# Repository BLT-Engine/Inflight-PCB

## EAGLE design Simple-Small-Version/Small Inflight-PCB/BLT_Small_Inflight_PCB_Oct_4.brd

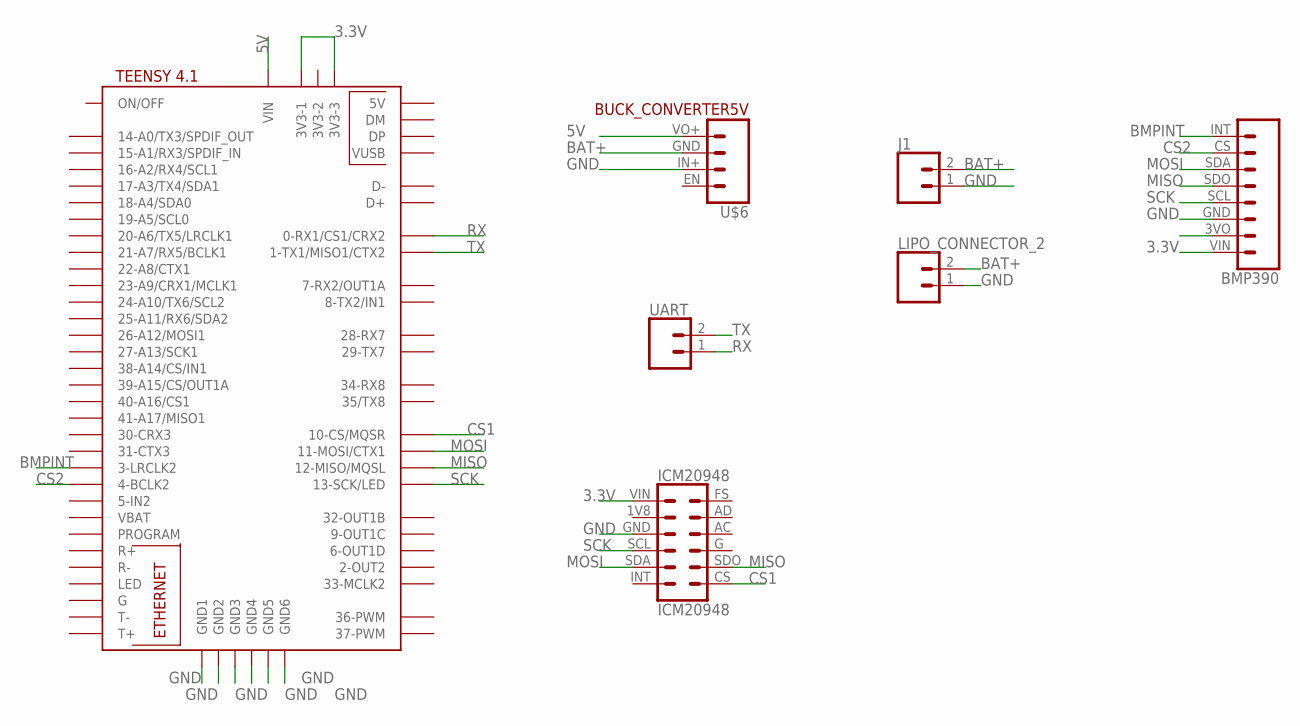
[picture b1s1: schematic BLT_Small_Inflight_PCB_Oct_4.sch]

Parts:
J1: CONN_02PTH4; 1X02_XTRA_BIG
LIPO_CONNECTOR_2: CONN_02; 1X02
U$1: TEENSY41
U$2: BMP390; MICROBUILDER_1X08_ROUND
U$3: ICM20948
U$6: BUCK_CONVERTER5V; 1X04
UART: CONN_02; 1X02

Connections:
3.3V: U$1.3V3-1, U$1.3V3-3, U$2.VIN, U$3.VIN
5V: U$1.VIN, U$6.VO+
BAT+: J1.2, LIPO_CONNECTOR_2.2, U$6.IN+
BMPINT: U$1.3-LRCLK2, U$2.INT
CS1: U$1.10-CS\MQSR (10-CS/MQSR), U$3.CS
CS2: U$1.4-BCLK2, U$2.CS
GND: J1.1, LIPO_CONNECTOR_2.1, U$1.GND1, U$1.GND2, U$1.GND3, U$1.GND4, U$1.GND5, U$1.GND6, U$2.GND, U$3.GND, U$6.GND
MISO: U$1.12-MISO/MQSL, U$2.SDO, U$3.SDO (SD0)
MOSI: U$1.11-MOSI/CTX1, U$2.SDA, U$3.SDA
RX: U$1.0-RX1/CS1/CRX2, UART.1
SCK: U$1.13-SCK/LED, U$2.SCL, U$3.SCL
TX: U$1.1-TX1/MISO1/CTX2, UART.2

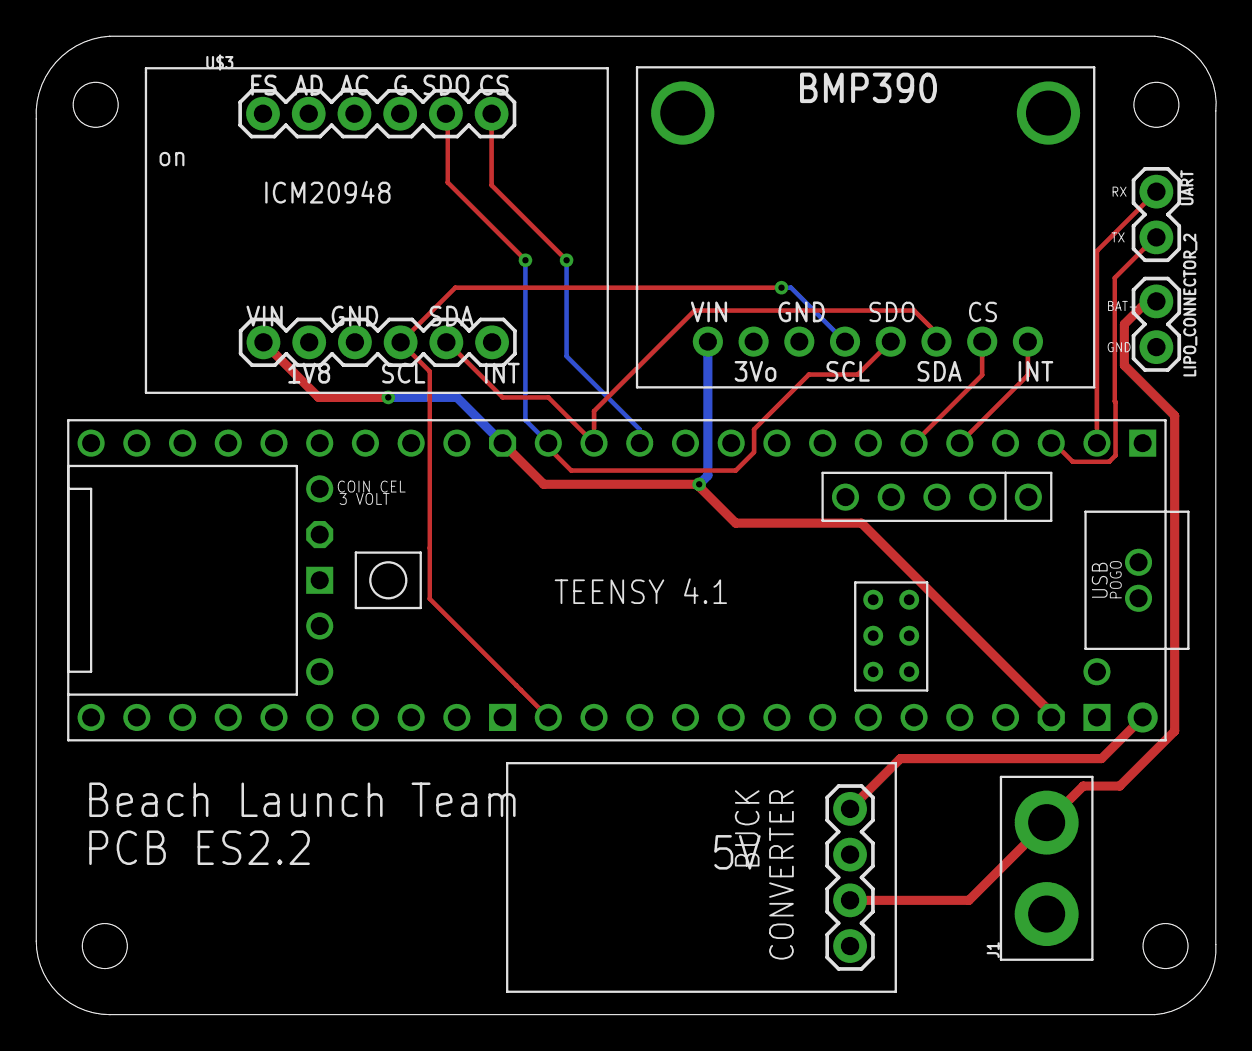
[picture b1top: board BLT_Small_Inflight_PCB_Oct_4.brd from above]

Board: 2 copper layers, 65.6 x 54.4 mm, 7 parts (0 on the bottom side), 12 nets.

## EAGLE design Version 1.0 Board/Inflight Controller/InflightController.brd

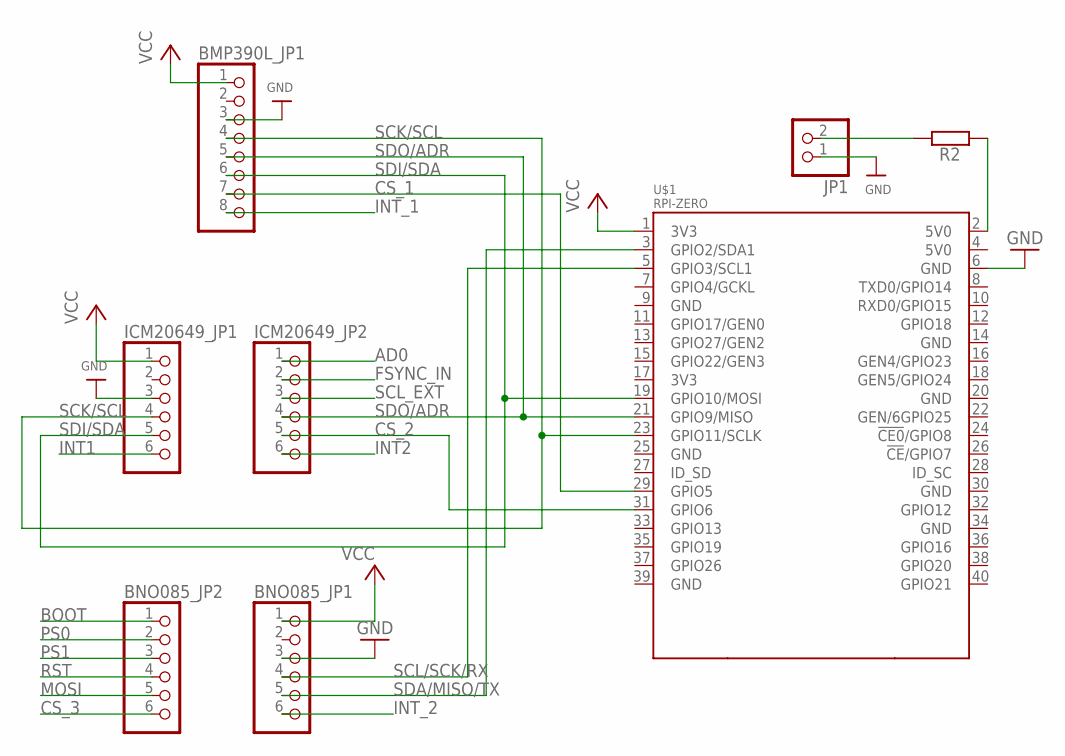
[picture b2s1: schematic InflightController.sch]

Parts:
BMP390L_JP1: HEADER-1X870MIL; 1X08_ROUND_70
BNO085_JP1, BNO085_JP2: HEADER-1X670MIL; 1X06_ROUND_70
ICM20649_JP1: HEADER-1X670MIL; 1X06_ROUND_70
ICM20649_JP2: HEADER-1X6ROUND; 1X06_ROUND
JP1: PINHD-1X2; 1X02
R2: SMK
U$1: RPI-ZERO; RASPBERRYPI_BASTELSTUBE_V13_RASPI_BOARD_B+_FULL

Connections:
5V0@1: R2.2, U$1.2 (5V0)
AD0: ICM20649_JP2.1
BOOT: BNO085_JP2.1
CS_1: BMP390L_JP1.7, U$1.29 (GPIO5)
CS_2: ICM20649_JP2.5, U$1.31 (GPIO6)
CS_3: BNO085_JP2.6
FSYNC_IN: ICM20649_JP2.2
GND: BMP390L_JP1.3, BNO085_JP1.3, ICM20649_JP1.3, JP1.1, U$1.6 (GND)
INT1: ICM20649_JP1.6
INT2: ICM20649_JP2.6
INT_1: BMP390L_JP1.8
INT_2: BNO085_JP1.6
MOSI: BNO085_JP2.5
unnamed: JP1.2, R2.1
PS0: BNO085_JP2.2
PS1: BNO085_JP2.3
RST: BNO085_JP2.4
SCK/SCL: BMP390L_JP1.4, ICM20649_JP1.4, U$1.23 (GPIO11/SCLK)
SCL/SCK/RX: BNO085_JP1.4, U$1.5 (GPIO3/SCL1)
SCL_EXT: ICM20649_JP2.3
SDA/MISO/TX: BNO085_JP1.5, U$1.3 (GPIO2/SDA1)
SDI/SDA: BMP390L_JP1.6, ICM20649_JP1.5, U$1.19 (GPIO10/MOSI)
SDO/ADR: BMP390L_JP1.5, ICM20649_JP2.4, U$1.21 (GPIO9/MISO)
VCC: BMP390L_JP1.1, BNO085_JP1.1, ICM20649_JP1.1, U$1.1 (3V3)

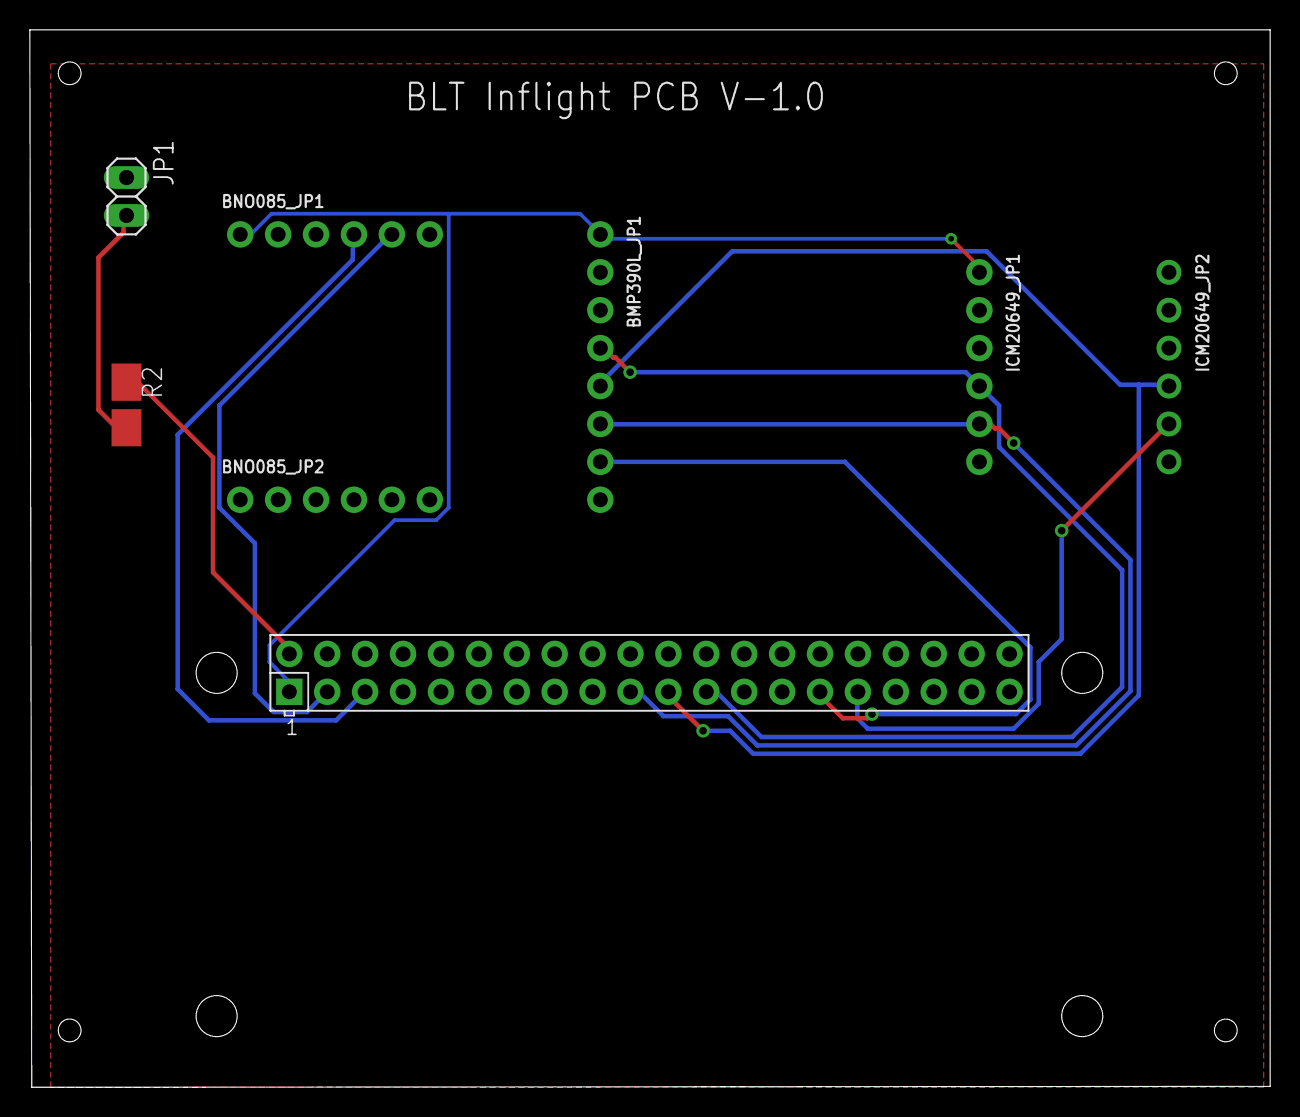
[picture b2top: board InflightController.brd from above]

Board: 2 copper layers, 83.1 x 70.9 mm, 8 parts (0 on the bottom side), 11 nets.

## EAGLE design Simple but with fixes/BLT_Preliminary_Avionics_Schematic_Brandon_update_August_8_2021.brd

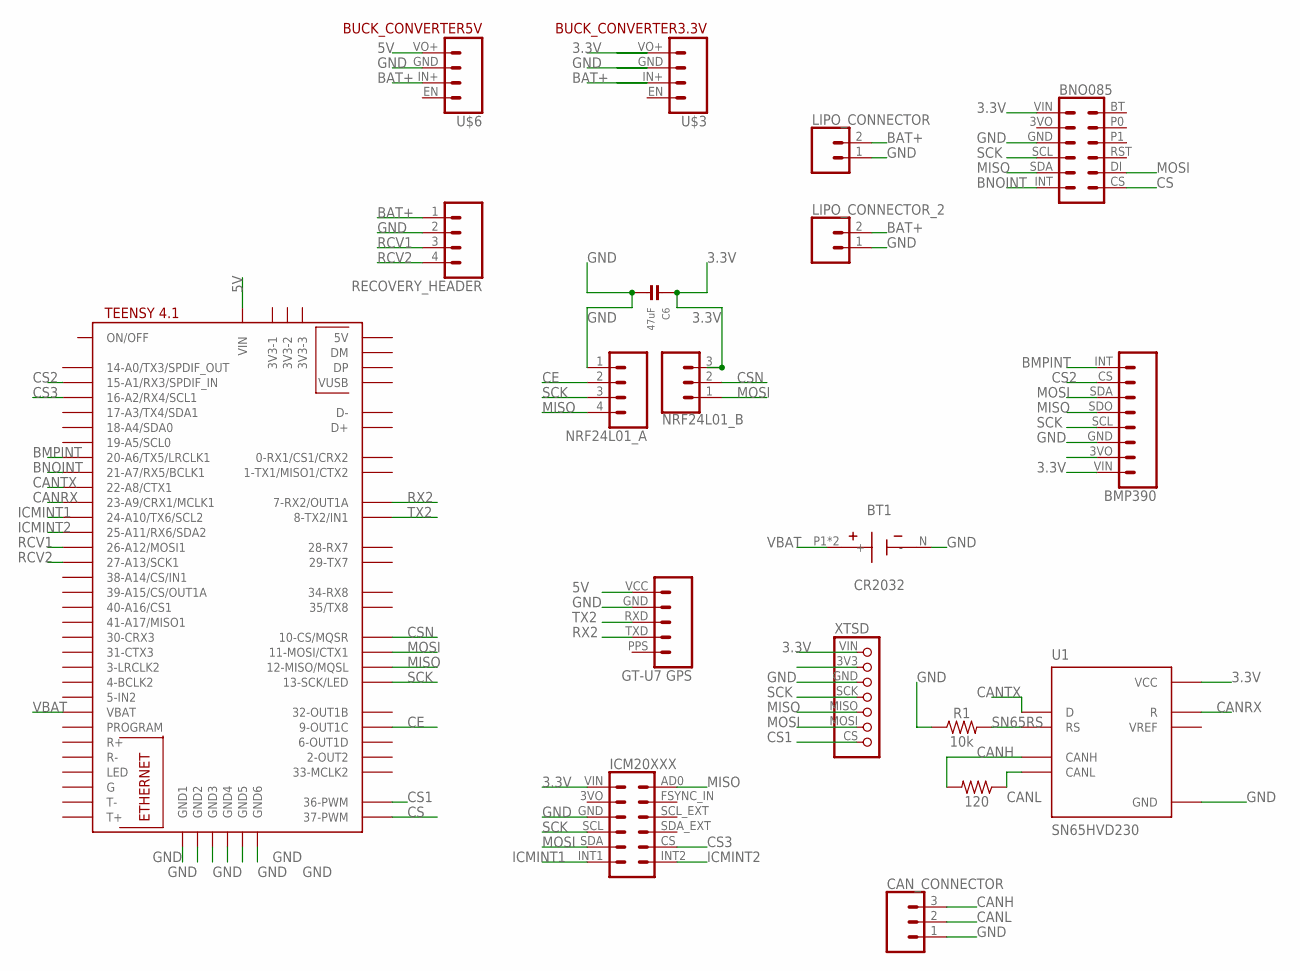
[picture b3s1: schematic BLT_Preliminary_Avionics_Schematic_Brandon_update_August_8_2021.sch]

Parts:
120: 1206
BT1: CR2032; BAT_3003
C6: 47uF; 0805
CAN_CONNECTOR: CONN_03; 1X03
LIPO_CONNECTOR: CONN_02PTH4; 1X02_XTRA_BIG
LIPO_CONNECTOR_2: CONN_02; 1X02
NRF24L01_A: CONN_04; 1X04
NRF24L01_B: CONN_03; 1X03
R1: 10k; 0603
RECOVERY_HEADER: CONN_04; 1X04
U1: SN65HVD230; SOIC127P599X175-8N
U$1: TEENSY41
U$2: BMP390; MICROBUILDER_1X08_ROUND
U$3: BUCK_CONVERTER3.3V; 1X04
U$4: GT-U7_GPS; 1X05
U$5: XTSDXTSD_PINS; 1X07
U$6: BUCK_CONVERTER5V; 1X04
U$7: BNO085; MICROBUILDER_1X06_ROUND_70
U$8: ICM20XXX; 1X06

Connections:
3.3V: C6.1, NRF24L01_B.3, U1.3 (VCC), U$2.VIN, U$3.VO+, U$5.VIN, U$7.VIN, U$8.VIN (VCC)
5V: U$1.VIN, U$4.VCC, U$6.VO+
BAT+: LIPO_CONNECTOR.2, LIPO_CONNECTOR_2.2, RECOVERY_HEADER.1, U$3.IN+, U$6.IN+
BMPINT: U$1.20-A6/TX5/LRCLK1, U$2.INT
BNOINT: U$1.21-A7/RX5/BCLK1, U$7.INT
CANH: 120.2, CAN_CONNECTOR.3, U1.7 (CANH)
CANL: 120.1, CAN_CONNECTOR.2, U1.6 (CANL)
CANRX: U1.4 (R), U$1.23-A9/CRX1/MCLK1
CANTX: U1.1 (D), U$1.22-A8/CTX1
CE: NRF24L01_A.2, U$1.9-OUT1C
CS: U$1.37-PWM, U$7.CS
CS1: U$1.36-PWM, U$5.CS
CS2: U$1.15-A1/RX3/SPDIF_IN, U$2.CS
CS3: U$1.16-A2/RX4/SCL1, U$8.CS
CSN: NRF24L01_B.2, U$1.10-CS\MQSR (10-CS/MQSR)
GND: BT1.N (-), C6.2, CAN_CONNECTOR.1, LIPO_CONNECTOR.1, LIPO_CONNECTOR_2.1, NRF24L01_A.1, R1.1, RECOVERY_HEADER.2, U1.2 (GND), U$1.GND1, U$1.GND2, U$1.GND3, U$1.GND4, U$1.GND5, U$1.GND6, U$2.GND, U$3.GND, U$4.GND, U$5.GND, U$6.GND, U$7.GND, U$8.GND
ICMINT1: U$1.24-A10/TX6/SCL2, U$8.INT1
ICMINT2: U$1.25-A11/RX6/SDA2, U$8.INT2
MISO: NRF24L01_A.4, U$1.12-MISO/MQSL, U$2.SDO, U$5.MISO, U$7.SDA, U$8.AD0
MOSI: NRF24L01_B.1, U$1.11-MOSI/CTX1, U$2.SDA, U$5.MOSI, U$7.DI, U$8.SDA
RCV1: RECOVERY_HEADER.3, U$1.26-A12/MOSI1
RCV2: RECOVERY_HEADER.4, U$1.27-A13/SCK1
RX2: U$1.7-RX2/OUT1A, U$4.TXD
SCK: NRF24L01_A.3, U$1.13-SCK/LED, U$2.SCL, U$5.SCK, U$7.SCL, U$8.SCL
SN65RS: R1.2, U1.8 (RS)
TX2: U$1.8-TX2/IN1, U$4.RXD
VBAT: BT1.P1 (+), BT1.P2 (+), U$1.VBAT

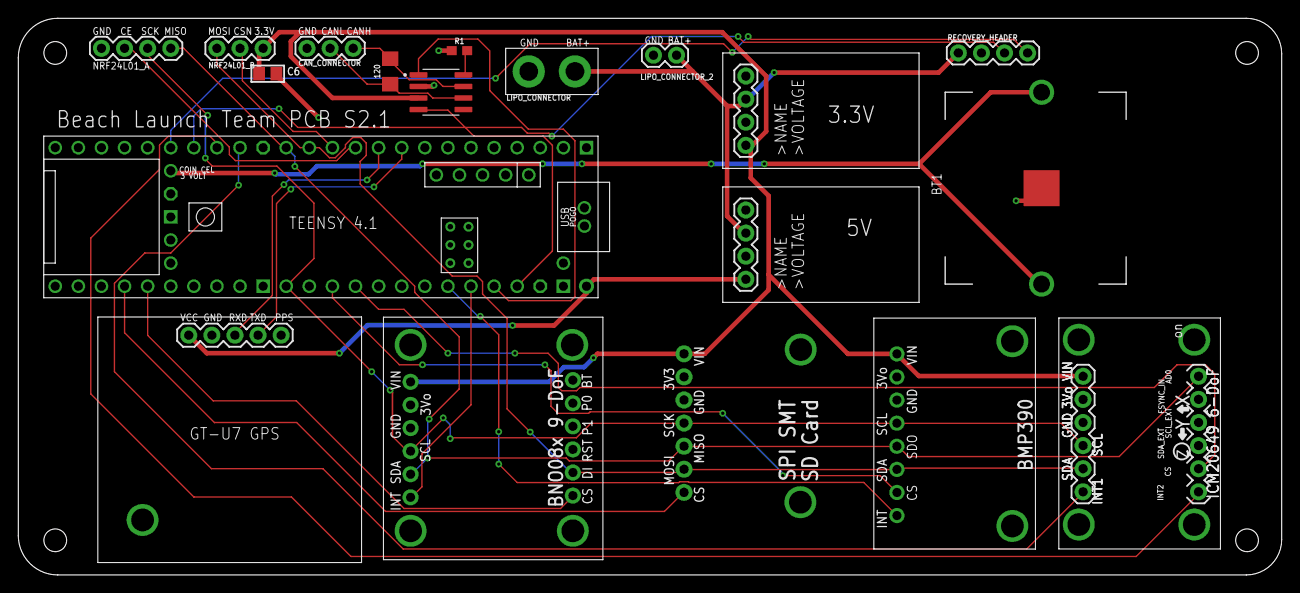
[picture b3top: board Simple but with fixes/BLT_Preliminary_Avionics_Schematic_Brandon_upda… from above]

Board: 2 copper layers, 138.9 x 61.2 mm, 19 parts (0 on the bottom side), 27 nets.

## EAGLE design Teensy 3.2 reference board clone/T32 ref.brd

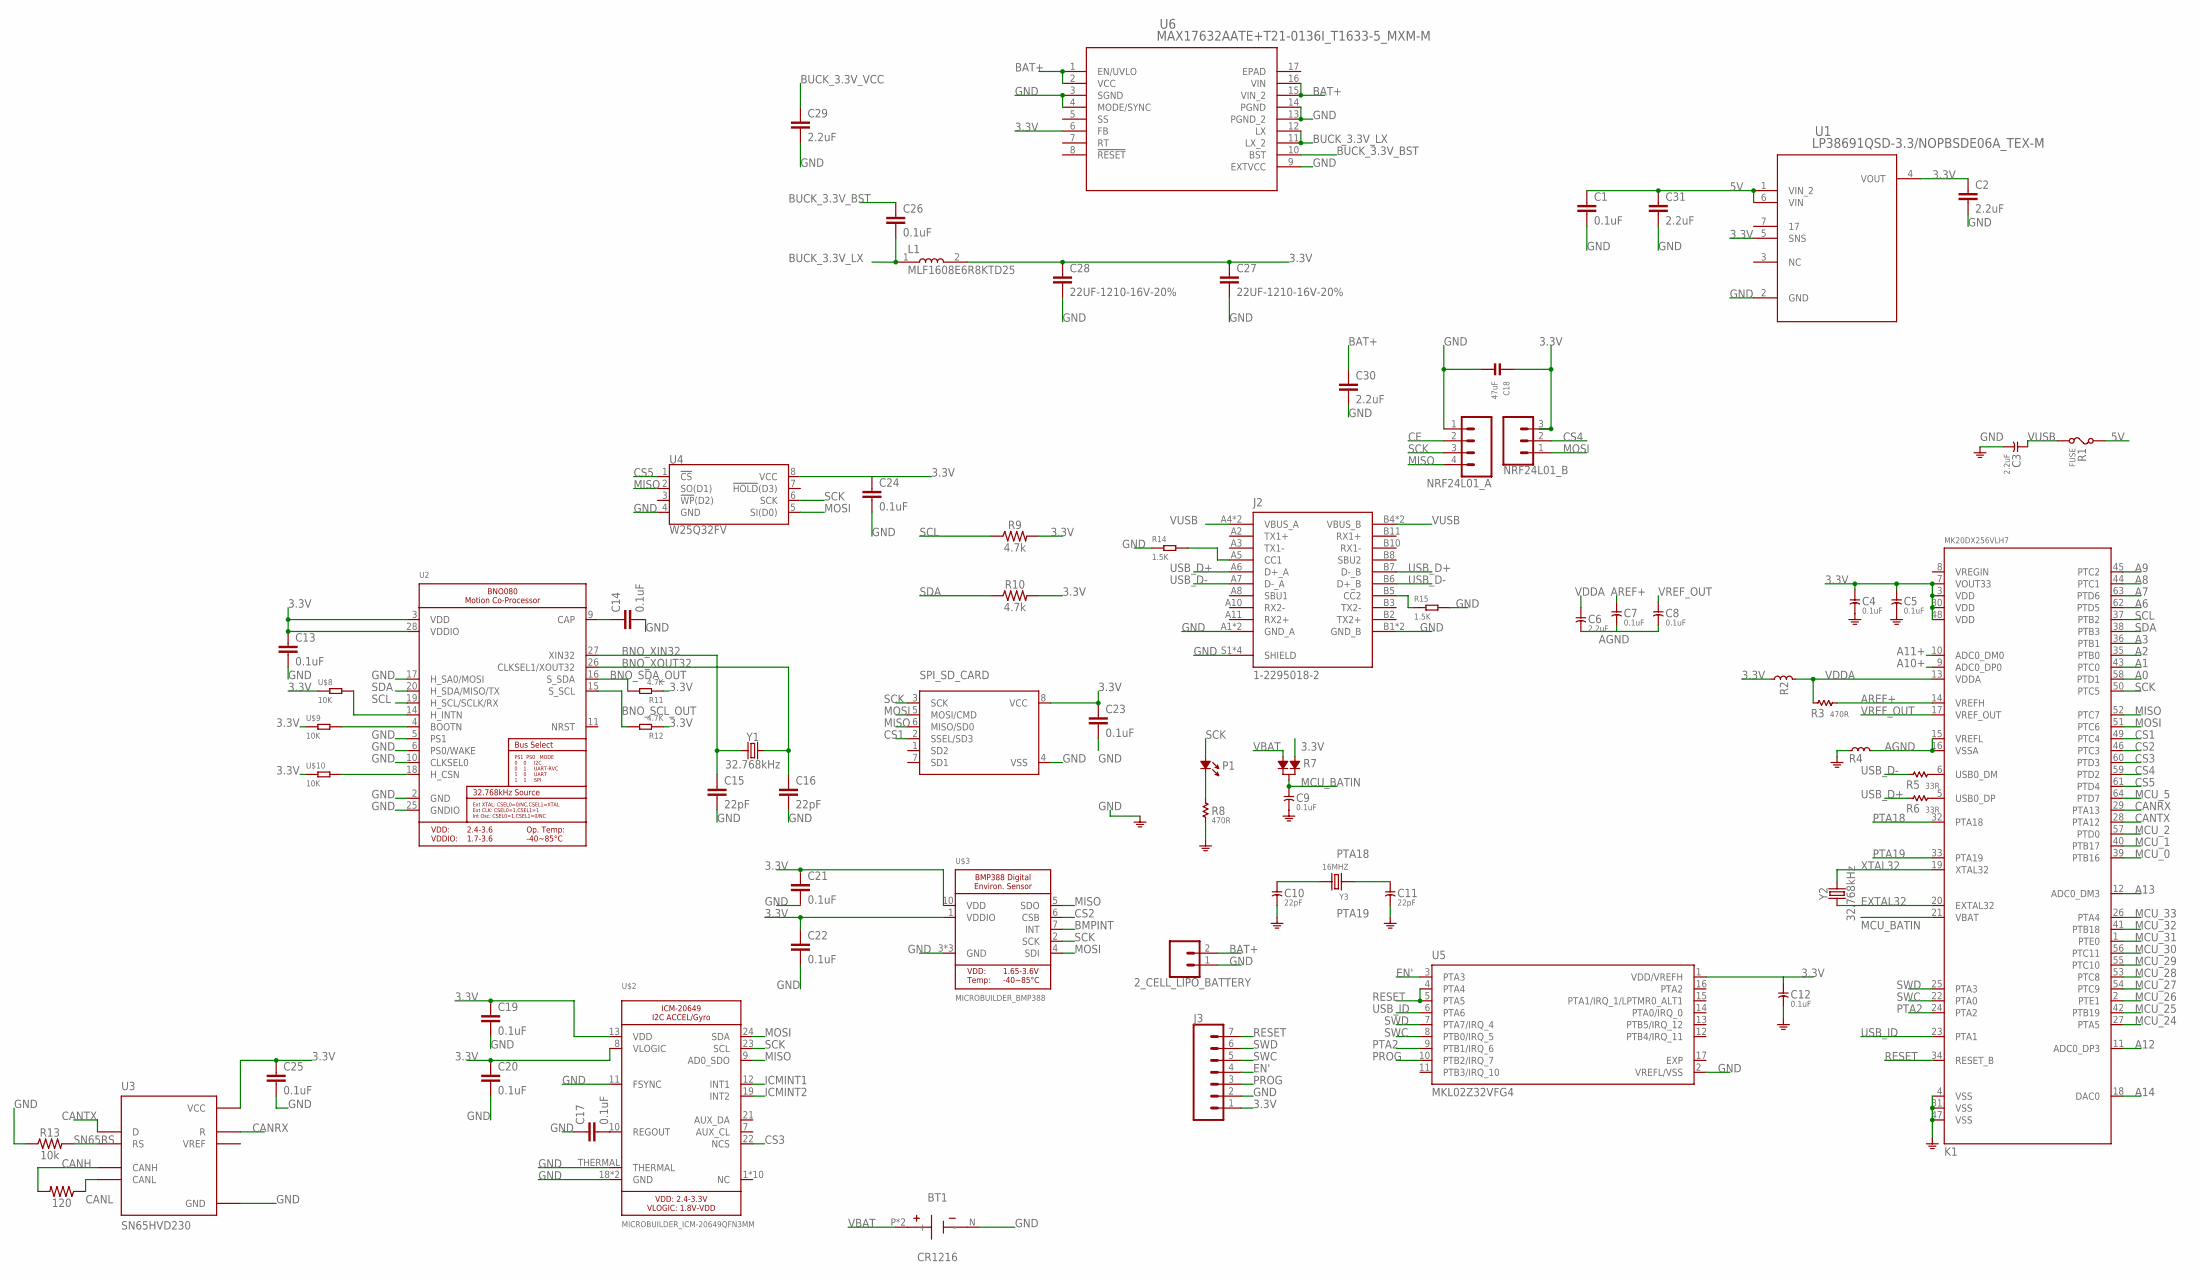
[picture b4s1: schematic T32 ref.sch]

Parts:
2_CELL_LIPO_BATTERY: CONN_02; 1X02
120: 1206
BT1: CR1216; BAT_3000
C1, C19, C20, C21, C22, C23, C24, C25, C26: 0.1uF; 0603
C2, C29, C30, C31: 2.2uF; 0603
C3, C6: 2.2uF; C0805
C4, C5, C7, C8, C9, C12: 0.1uF; C0603
C10, C11: 22pF; C0603
C13, C14, C17: 0.1uF; 0402
C15, C16: 22pF; 0603
C18: 47uF; 0805
C27, C28: 22UF-1210-16V-20%; 1210
J2: 1-2295018-2; TE_1-2295018-2
J3: CONN_07; 1X07
K1: MK20DX256VLH7; LQFP64-05
L1: MLF1608E6R8KTD25; INDC1608X95N
NRF24L01_A: CONN_04; 1X04
NRF24L01_B: CONN_03; 1X03
P1: LED; LED-0805
R1: FUSE; F0805
R2, R4: FERRITE; L0603
R3, R8: 470R; R0603
R5, R6: 33R; R0603
R7: DIODE_DUAL; SOT-23
R9, R10: 4.7k; 0603
R11, R12: 4.7K; R0402
R13: 10k; 0603
R14, R15: 1.5K; R0603
SPI_SD_CARD: MICROBUILDER_SMT_SDCARD_8PIN; MICROBUILDER_LGA8_8X6
U1: LP38691QSD-3.3/NOPBSDE06A_TEX-M; SDE06A_TEX-M
U2: MICROBUILDER_BNO080
U3: SN65HVD230; SOIC127P599X175-8N
U4: W25Q32FV; WSON8-6X5MM
U5: MKL02Z32VFG4; QFN50P300X300X65-17N
U6: MAX17632AATE+T21-0136I_T1633-5_MXM-M; 21-0136I_T1633-5_MXM-M
U$2: MICROBUILDER_ICM-20649QFN3MM; MICROBUILDER_QFN24_3MM
U$3: MICROBUILDER_BMP388
U$8, U$9, U$10: 10K; R0402
Y1, Y2: 32.768kHz; CRYSTAL-SMD-3.2X1.5MM
Y3: 16MHZ; X2-SMD-5.0X3.2X1.3MM

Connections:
3.3V: C2.1, C4.1, C5.1, C12.1, C13.1, C18.1, C19.1, C20.1, C21.1, C22.1, C23.1, C24.1, C25.1, C27.1, C28.1, J3.1, K1.3 (VDD), K1.7 (VOUT33), K1.30 (VDD), K1.48 (VDD), L1.2, NRF24L01_B.3, R2.1, R7.1, R9.2, R10.2, R11.1, R12.1, SPI_SD_CARD.8 (VCC), U1.4 (VOUT), U1.5 (SNS), U2.3 (VDD), U2.28 (VDDIO), U3.3 (VCC), U4.8 (VCC), U5.1 (VDD/VREFH), U6.6 (FB), U$2.8 (VLOGIC), U$2.13 (VDD), U$3.1 (VDDIO), U$3.10 (VDD), U$8.1, U$9.1, U$10.1
5V: C1.1, C31.1, R1.2, U1.1 (VIN_2), U1.6 (VIN)
A0: K1.58 (PTD1)
A1: K1.43 (PTC0)
A2: K1.35 (PTB0)
A3: K1.36 (PTB1)
A6: K1.62 (PTD5)
A7: K1.63 (PTD6)
A8: K1.44 (PTC1)
A9: K1.45 (PTC2)
A10+: K1.9 (ADC0_DP0)
A11+: K1.10 (ADC0_DM0)
A12: K1.11 (ADC0_DP3)
A13: K1.12 (ADC0_DM3)
A14: K1.18 (DAC0)
AGND: C6.2, C7.2, C8.2, K1.15 (VREFL), K1.16 (VSSA), R4.2
AREF+: C7.1, K1.14 (VREFH), R3.2
BAT+: 2_CELL_LIPO_BATTERY.2, C30.1, U6.1 (EN/UVLO), U6.2 (VCC), U6.15 (VIN_2), U6.16 (VIN)
BMPINT: U$3.7 (INT)
BNO_SCL_OUT: R12.2, U2.15 (S_SCL)
BNO_SDA_OUT: R11.2, U2.16 (S_SDA)
BNO_XIN32: C15.1, U2.27 (XIN32), Y1.P$1 (1)
BNO_XOUT32: C16.1, U2.26 (CLKSEL1/XOUT32), Y1.P$2 (2)
BUCK_3.3V_BST: C26.1, U6.10 (BST)
BUCK_3.3V_LX: C26.2, L1.1, U6.11 (LX_2), U6.12 (LX)
BUCK_3.3V_VCC: C29.1
CANH: 120.2, U3.7 (CANH)
CANL: 120.1, U3.6 (CANL)
CANRX: K1.29 (PTA13), U3.4 (R)
CANTX: K1.28 (PTA12), U3.1 (D)
CE: NRF24L01_A.2
CS1: K1.49 (PTC4), SPI_SD_CARD.2 (SSEL/SD3)
CS2: K1.46 (PTC3), U$3.6 (CSB)
CS3: K1.60 (PTD3), U$2.22 (NCS)
CS4: K1.59 (PTD2), NRF24L01_B.2
CS5: K1.61 (PTD4), U4.1 (!CS!)
EN': J3.4, U5.3 (PTA3)
EXP: U5.17 (EXP)
EXTAL32: K1.20 (EXTAL32), Y2.P$1 (1)
GND: 2_CELL_LIPO_BATTERY.1, BT1.N (-), C1.2, C2.2, C3.2, C4.2, C5.2, C9.2, C10.2, C11.2, C12.2, C13.2, C14.2, C15.2, C16.2, C17.1, C18.2, C19.2, C20.2, C21.2, C22.2, C23.2, C24.2, C25.2, C27.2, C28.2, C29.2, C30.2, C31.2, J2.A1 (GND_A), J2.A12 (GND_A), J2.B1 (GND_B), J2.B12 (GND_B), J2.S1 (SHIELD), J2.S2 (SHIELD), J2.S3 (SHIELD), J2.S4 (SHIELD), J3.2, K1.4 (VSS), K1.31 (VSS), K1.47 (VSS), NRF24L01_A.1, R4.1, R8.1, R13.1, R14.1, R15.2, SPI_SD_CARD.4 (VSS), U1.2 (GND), U2.2 (GND), U2.5 (PS1), U2.6 (PS0/WAKE), U2.10 (CLKSEL0), U2.17 (H_SA0/MOSI), U2.25 (GNDIO), U3.2 (GND), U4.4 (GND), U5.2 (VREFL/VSS), U6.3 (SGND), U6.4 (MODE/SYNC), U6.9 (EXTVCC), U6.13 (PGND_2), U6.14 (PGND), U$2.11 (FSYNC), U$2.18 (GND), U$2.20 (GND), U$2.THERMAL, U$3.3 (GND), U$3.8 (GND), U$3.9 (GND)
ICMINT1: U$2.12 (INT1)
ICMINT2: U$2.19 (INT2)
MCU_0: K1.39 (PTB16)
MCU_1: K1.40 (PTB17)
MCU_2: K1.57 (PTD0)
MCU_5: K1.64 (PTD7)
MCU_24: K1.27 (PTA5)
MCU_25: K1.42 (PTB19)
MCU_26: K1.2 (PTE1)
MCU_27: K1.54 (PTC9)
MCU_28: K1.53 (PTC8)
MCU_29: K1.55 (PTC10)
MCU_30: K1.56 (PTC11)
MCU_31: K1.1 (PTE0)
MCU_32: K1.41 (PTB18)
MCU_33: K1.26 (PTA4)
MCU_BATIN: C9.1, K1.21 (VBAT), R7.3
MISO: K1.52 (PTC7), NRF24L01_A.4, SPI_SD_CARD.6 (MISO/SD0), U4.2 (SO(D1)), U$2.9 (AD0_SDO), U$3.5 (SDO)
MOSI: K1.51 (PTC6), NRF24L01_B.1, SPI_SD_CARD.5 (MOSI/CMD), U4.5 (SI(D0)), U$2.24 (SDA), U$3.4 (SDI)
unnamed: J2.A5 (CC1), R14.2
unnamed: J2.B5 (CC2), R15.1
unnamed: C14.1, U2.9 (CAP)
unnamed: K1.5 (USB0_DP), R6.2
unnamed: K1.6 (USB0_DM), R5.2
unnamed: P1.-, R8.2
unnamed: C17.2, U$2.10 (REGOUT)
unnamed: U2.18 (H_CSN), U$10.2
unnamed: U2.14 (H_INTN), U$8.2
unnamed: U2.4 (BOOTN), U$9.2
PROG: J3.3, U5.10 (PTB2/IRQ_7)
PTA2: K1.24 (PTA2), U5.9 (PTB1/IRQ_6)
PTA18: C10.1, K1.32 (PTA18), Y3.2
PTA19: C11.1, K1.33 (PTA19), Y3.1
RESET: J3.7, K1.34 (RESET_B), U5.4 (PTA4), U5.5 (PTA5)
SCK: K1.50 (PTC5), NRF24L01_A.3, P1.+, SPI_SD_CARD.3 (SCK), U4.6 (SCK), U$2.23 (SCL), U$3.2 (SCK)
SCL: K1.37 (PTB2), R9.1, U2.19 (H_SCL/SCLK/RX)
SDA: K1.38 (PTB3), R10.1, U2.20 (H_SDA/MISO/TX)
SN65RS: R13.2, U3.8 (RS)
SWC: J3.5, K1.22 (PTA0), U5.8 (PTB0/IRQ_5)
SWD: J3.6, K1.25 (PTA3), U5.7 (PTA7/IRQ_4)
USB_D+: J2.A6 (D+_A), J2.B7 (D-_B), R6.1
USB_D-: J2.A7 (D-_A), J2.B6 (D+_B), R5.1
USB_ID: K1.23 (PTA1), U5.6 (PTA6)
VBAT: BT1.P (+), BT1.P1 (+), R7.2
VDDA: C6.1, K1.13 (VDDA), R2.2, R3.1
VREF_OUT: C8.1, K1.17 (VREF_OUT)
VUSB: C3.1, J2.A4 (VBUS_A), J2.A9 (VBUS_A), J2.B4 (VBUS_B), J2.B9 (VBUS_B), R1.1
XTAL32: K1.19 (XTAL32), Y2.P$2 (2)

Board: 2 copper layers, 71 parts (0 on the bottom side), 55 nets, no tracks yet.

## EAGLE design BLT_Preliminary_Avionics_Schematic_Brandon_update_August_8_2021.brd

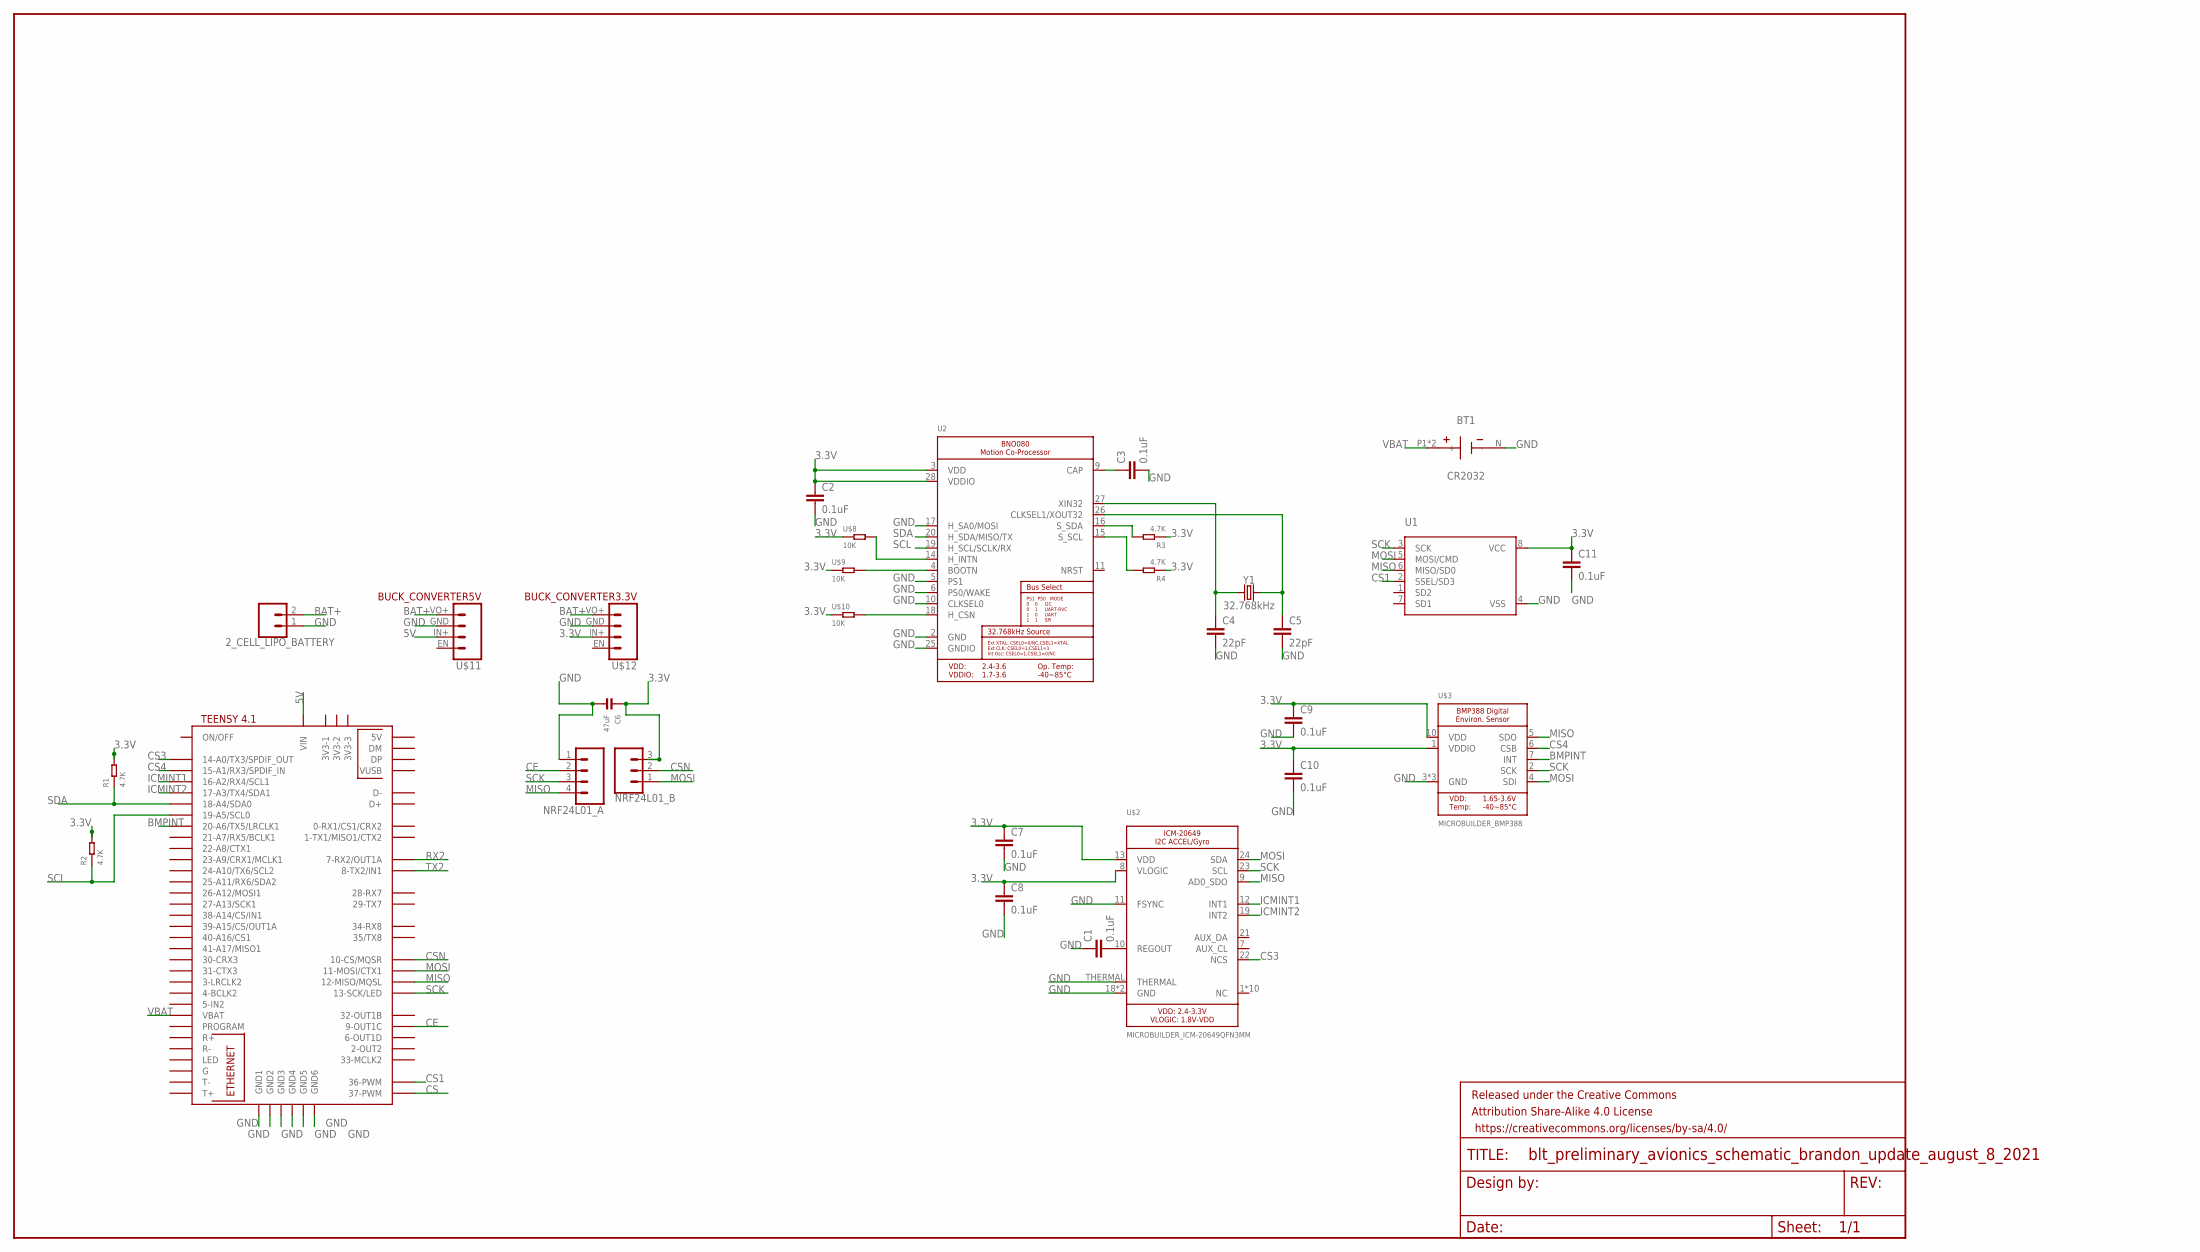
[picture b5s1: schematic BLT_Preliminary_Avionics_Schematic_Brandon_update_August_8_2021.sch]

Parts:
2_CELL_LIPO_BATTERY: CONN_02; 1X02
BT1: CR2032; BAT_3003
C1, C2, C3: 0.1uF; 0402
C4, C5: 22pF; 0603
C6: 47uF; 0805
C7, C8, C9, C10, C11: 0.1uF; 0603
FRAME1: FRAME-LEDGER; CREATIVE_COMMONS
NRF24L01_A: CONN_04; 1X04
NRF24L01_B: CONN_03; 1X03
R1, R2, R3, R4: 4.7K; R0402
U1: MICROBUILDER_SMT_SDCARD_8PIN; MICROBUILDER_LGA8_8X6
U2: MICROBUILDER_BNO080
U$1: TEENSY41
U$2: MICROBUILDER_ICM-20649QFN3MM; MICROBUILDER_QFN24_3MM
U$3: MICROBUILDER_BMP388
U$8, U$9, U$10: 10K; R0402
U$11: BUCK_CONVERTER5V; 1X04
U$12: BUCK_CONVERTER3.3V; 1X04
Y1: 32.768kHz; CRYSTAL-SMD-3.2X1.5MM

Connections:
3.3V: C2.1, C6.1, C7.1, C8.1, C9.1, C10.1, C11.1, NRF24L01_B.3, R1.2, R2.2, R3.1, R4.1, U1.8 (VCC), U2.3 (VDD), U2.28 (VDDIO), U$2.8 (VLOGIC), U$2.13 (VDD), U$3.1 (VDDIO), U$3.10 (VDD), U$8.1, U$9.1, U$10.1, U$12.IN+
5V: U$1.VIN, U$11.IN+
BAT+: 2_CELL_LIPO_BATTERY.2, U$11.VO+, U$12.VO+
BMPINT: U$1.20-A6/TX5/LRCLK1, U$3.7 (INT)
CE: NRF24L01_A.2, U$1.9-OUT1C
CS: U$1.37-PWM
CS1: U1.2 (SSEL/SD3), U$1.36-PWM
CS3: U$1.14-A0/TX3/SPDIF_OUT, U$2.22 (NCS)
CS4: U$1.15-A1/RX3/SPDIF_IN, U$3.6 (CSB)
CSN: NRF24L01_B.2, U$1.10-CS\MQSR (10-CS/MQSR)
GND: 2_CELL_LIPO_BATTERY.1, BT1.N (-), C1.1, C2.2, C3.2, C4.2, C5.2, C6.2, C7.2, C8.2, C9.2, C10.2, C11.2, NRF24L01_A.1, U1.4 (VSS), U2.2 (GND), U2.5 (PS1), U2.6 (PS0/WAKE), U2.10 (CLKSEL0), U2.17 (H_SA0/MOSI), U2.25 (GNDIO), U$1.GND1, U$1.GND2, U$1.GND3, U$1.GND4, U$1.GND5, U$1.GND6, U$2.11 (FSYNC), U$2.18 (GND), U$2.20 (GND), U$2.THERMAL, U$3.3 (GND), U$3.8 (GND), U$3.9 (GND), U$11.GND, U$12.GND
ICMINT1: U$1.16-A2/RX4/SCL1, U$2.12 (INT1)
ICMINT2: U$1.17-A3/TX4/SDA1, U$2.19 (INT2)
MISO: NRF24L01_A.4, U1.6 (MISO/SD0), U$1.12-MISO/MQSL, U$2.9 (AD0_SDO), U$3.5 (SDO)
MOSI: NRF24L01_B.1, U1.5 (MOSI/CMD), U$1.11-MOSI/CTX1, U$2.24 (SDA), U$3.4 (SDI)
unnamed: C1.2, U$2.10 (REGOUT)
unnamed: C4.1, U2.27 (XIN32), Y1.P$1 (1)
unnamed: R3.2, U2.16 (S_SDA)
unnamed: C5.1, U2.26 (CLKSEL1/XOUT32), Y1.P$2 (2)
unnamed: U2.18 (H_CSN), U$10.2
unnamed: R4.2, U2.15 (S_SCL)
unnamed: U2.14 (H_INTN), U$8.2
unnamed: U2.4 (BOOTN), U$9.2
unnamed: C3.1, U2.9 (CAP)
RX2: U$1.7-RX2/OUT1A
SCK: NRF24L01_A.3, U1.3 (SCK), U$1.13-SCK/LED, U$2.23 (SCL), U$3.2 (SCK)
SCL: R2.1, U2.19 (H_SCL/SCLK/RX), U$1.19-A5/SCL0
SDA: R1.1, U2.20 (H_SDA/MISO/TX), U$1.18-A4/SDA0
TX2: U$1.8-TX2/IN1
VBAT: BT1.P1 (+), BT1.P2 (+), U$1.VBAT

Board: 2 copper layers, 35 parts (0 on the bottom side), 27 nets, no tracks yet.

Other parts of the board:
U$4, U$5, U$6, U$7: MICROBUILDER_MOUNTINGHOLE_2.5_NPH

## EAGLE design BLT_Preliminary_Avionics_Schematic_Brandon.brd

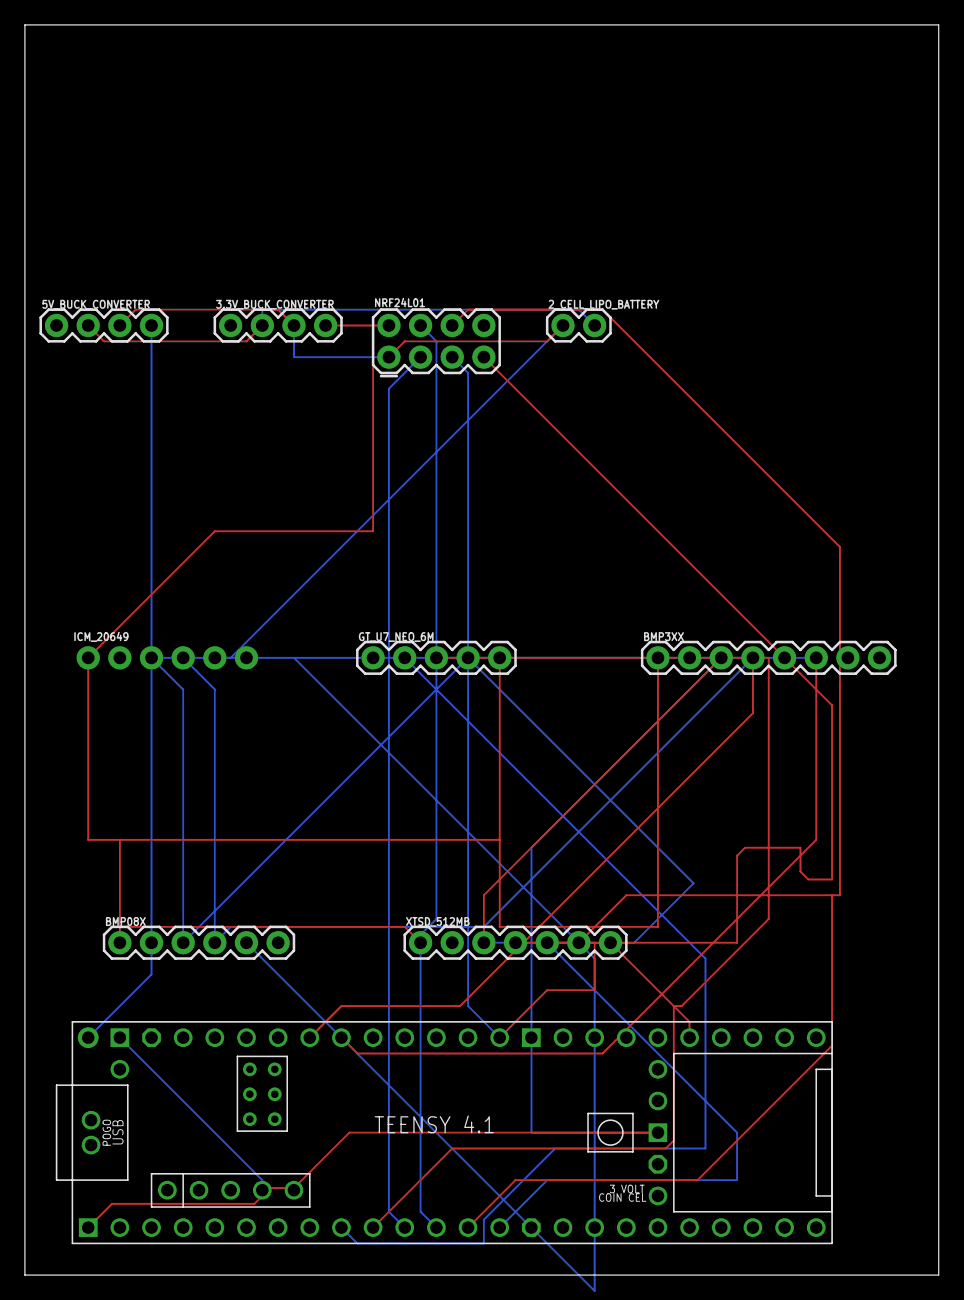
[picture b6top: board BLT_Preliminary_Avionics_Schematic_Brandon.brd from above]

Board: 2 copper layers, 73.3 x 100.3 mm, 10 parts (0 on the bottom side), 14 nets.

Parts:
2_CELL_LIPO_BATTERY: 1X02
3.3V_BUCK_CONVERTER, 5V_BUCK_CONVERTER: 1X04
BMP3XX: 1X08
BMP08X: 1X06
GT_U7_NEO_6M: 1X05
ICM_20649: 1X06_NO_SILK
NRF24L01: 2X4
U$1: TEENSY41
XTSD_512MB: 1X07

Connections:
3.3V: 3.3V_BUCK_CONVERTER.4, BMP3XX.1, BMP08X.1, GT_U7_NEO_6M.5, ICM_20649.1, NRF24L01.2, XTSD_512MB.1
5V: 5V_BUCK_CONVERTER.4, U$1.VIN
BAT+: 2_CELL_LIPO_BATTERY.2, 3.3V_BUCK_CONVERTER.2, 5V_BUCK_CONVERTER.2
CE: NRF24L01.3, U$1.9-OUT1C
CS: U$1.37-PWM, XTSD_512MB.7
CSN: NRF24L01.4, U$1.10-CS\MQSR
GND: 2_CELL_LIPO_BATTERY.1, 3.3V_BUCK_CONVERTER.3, 5V_BUCK_CONVERTER.3, BMP3XX.3, BMP08X.3, GT_U7_NEO_6M.4, ICM_20649.3, NRF24L01.1, U$1.GND1, U$1.GND2, U$1.GND3, U$1.GND4, U$1.GND5, U$1.GND6, XTSD_512MB.3
MISO: NRF24L01.7, U$1.12-MISO/MQSL, XTSD_512MB.5
MOSI: NRF24L01.6, U$1.11-MOSI/CTX1, XTSD_512MB.6
RX2: GT_U7_NEO_6M.2, U$1.7-RX2/OUT1A
SCK: NRF24L01.5, U$1.13-SCK/LED, XTSD_512MB.4
SCL: BMP3XX.4, BMP08X.4, ICM_20649.4, U$1.19-A5/SCL0
SDA: BMP3XX.6, BMP08X.5, ICM_20649.5, U$1.18-A4/SDA0
TX2: GT_U7_NEO_6M.3, U$1.8-TX2/IN1

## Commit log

2021-04-24 Inflight PCB Controller V.1
    Andrew Logue - 4/24/2021
2021-05-20 Updated Inflight Controller
    5/19/21
2021-05-20 Inflight Controller Board and Schematic
    5/20/21
2021-05-24 Fixed CS routing error
    5/23/21
2021-05-24 Fixed VCC routing from PI
    5/24/21
2021-05-24 Fixed more traces
    5/24/21
2021-08-11 Updated for current board design
2021-08-11 Updated files
2021-08-16 updated files even more
2021-08-25 Updated more files
2021-08-25 files updated
2021-08-28 Updated info
2021-08-29 Updated footprints
2021-08-30 updated mor files
2021-10-07 Updated layout
2022-04-27 Updated board

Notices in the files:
parts and their libraries:
SparkFun-Connectors: Licensing: Creative Commons ShareAlike 4.0 International - https://creativecommons.org/licenses/by-sa/4.0
SparkFun-Aesthetics: Released under the Creative Commons Attribution Share-Alike 4.0 License
SparkFun-Aesthetics: https://creativecommons.org/licenses/by-sa/4.0
